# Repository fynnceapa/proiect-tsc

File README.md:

# OpenBook Project for Systems Testing
# Stan Andrei Razvan (Group 333CA)  

## Block Diagram

## Steps took
I followed the schematic and board layout provided by the teacher as closely as I could in Fusion 360.

The problems started when I began placing the components on the board. Most of the difficulties were related to identifying which discrete components to place and where, in order to make the routing process easier and more efficient.

I decided to route the board using two layers—top and bottom—and used vias where necessary. My lack of routing skills comes from the fact that i did not play around in Fusion that much...

## Core Components  

### 1. ESP32-C6 Microcontroller (Main Board)  
- **Processor:** 32-bit RISC-V @ 160MHz  
- **Wireless:** Wi-Fi 6 (802.11ax) + Bluetooth 5  
- **Memory:**  
  - 320KB RAM  
  - 512KB internal Flash (expandable via external NOR Flash)  
- **I/O:** 30+ GPIOs supporting SPI, I2C, UART, USB 2.0  

### 2. Peripheral Modules  

| Module          | Interface | Speed       | Key ESP32-C6 Pins       |  
|-----------------|-----------|-------------|-------------------------|  
| E-Paper Display | SPI       | 10-40 MHz   | `EPD_CS`, MOSI, SCK     |  
| BME688 Sensor   | I2C       | 400 kHz     | SCL, SDA                |  
| DS3231 RTC      | I2C       | 100 kHz     | SCL, SDA                |  
| NOR Flash       | SPI/QSPI  | 133 MHz     | `FLASH_CS`, MOSI, SCK   |  
| SD Card         | SPI       | 25 MHz      | `SS_SD`, MOSI, SCK      |  

## Module Specifications  

### A. E-Paper Display  
- **Type:** SPI-based (e.g., Waveshare)  
- **Key Pins:**  
  - `EPD_RST`: Hardware reset  
  - `EPD_DC`: Data/command control  
  - `EPD_BUSY`: Status monitoring  
- **Power:**  
  - 150mA (active refresh)  
  - 0mA (static display)  

### B. BME688 Environmental Sensor  
- **Metrics:** Temperature, humidity, pressure, VOC  
- **Accuracy:** ±0.5°C, ±3% RH  
- **Power:** 3.6mA (active), 2.1µA (sleep)  

### C. DS3231 Real-Time Clock  
- **Precision:** ±2ppm (±1min/year)  
- **Features:** Battery backup (`VBAT`), alarm interrupts (`INT_RTC`)  

### D. Storage Systems  
- **NOR Flash (W25Q512JVEIQ):**  
  - 64MB capacity  
  - QSPI @ 133MHz  
- **SD Card:**  
  - SPI interface @ 25MHz  

### E. Power Management  
- **Charger:** MCP73831 (Li-Po, 5V USB → 4.2V)  
- **LDO Regulator:** XC6220A331MR-G (3.3V logic)  
- **Battery Monitor:** MAX17048G+T10 (I2C)  

## Power Analysis  
| Mode             | Current Draw | Runtime* |  
|------------------|--------------|----------|  
| Active Operation | ~230mA       | ~4h      |  
| Deep Sleep       | ~6µA         | ~2 years |  

*With 1000mAh Li-Po battery  

## Low-Power Design Strategies  
- Deep-sleep mode with RTC wake-up  
- Selective peripheral power control  
- SPI/I2C bus deactivation when idle  

## Pinout Summary  

| Function            | Key Pins                 | Purpose                          |  
|---------------------|--------------------------|----------------------------------|  
| **E-Paper**         | `EPD_CS`, `EPD_DC`       | Display control                  |  
| **NOR Flash**       | `FLASH_CS`               | External memory access           |  
| **RTC**            | `INT_RTC`, `32KHZ`       | Timekeeping & alarms             |  
| **BME688**         | `SCL`, `SDA`             | Environmental sensing            |  
| **Power**          | `VBAT`, `3V3`            | Battery & regulated power        |

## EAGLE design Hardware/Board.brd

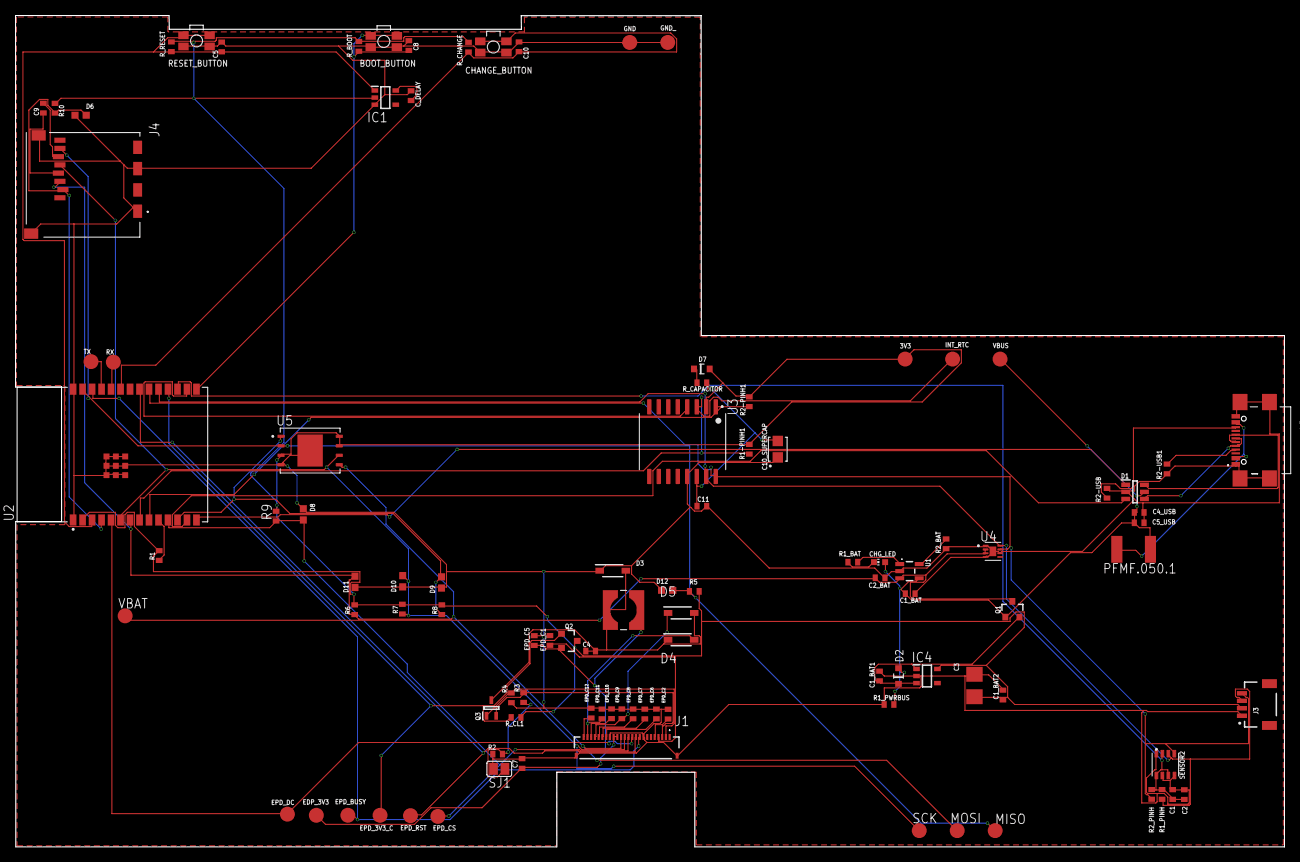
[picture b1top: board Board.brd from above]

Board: 2 copper layers, 169.8 x 111.2 mm, 103 parts (0 on the bottom side), 56 nets.

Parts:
3V3: TPTP20R; TP20R
BOOT_BUTTON: BUTTON_CUSYOMV1; MYBUTTON
C1, C2: 100nF; ESP32_WROVER_EAGLE-LTSPICE_C0402
C1_BAT, C1_BAT1, C1_BAT2, C2_BAT, C5_USB: 4.7uF; EAGLE-LTSPICE_C0402
C3: 100uF TANT; RCL_CT3528
C4: 4.7uF/25V; EAGLE-LTSPICE_C0402
C4_USB, C8, C10, C11: 100nF; EAGLE-LTSPICE_C0402
C5: 1uF; EAGLE-LTSPICE_C0402
C7: 10uF; EAGLE-LTSPICE_C0402
C9: EAGLE-LTSPICE_C0402
C10_SUPERCAP: CPH3225A; CAPCP3225X100N
CHANGE_BUTTON: BUTTON_CUSYOMV1; MYBUTTON
CHG_LED: ADAFRUIT_CHIP-LED0603
C_DELAY: 100nF; EAGLE-LTSPICE_C0402
D1: USBLC6-2SC6Y; SOT95P280X145-6N
D2, D7: ESP32_WROVER_AVX---SD0805S020S1R0_AVX_SD0805S020S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; ESP32_WROVER_AVX---SD0805S020S1R0_AVX_SD0805S020S1R0_0
D3, D4, D5: MBR0530; SOD3716X135N
D6, D8, D9, D10, D11, D12: PGB1010603MR; DIOC1608X36N
EDP_3V3: TPTP20R; TP20R
EPD_3V3_C: TPTP20R; TP20R
EPD_BUSY: TPTP20R; TP20R
EPD_C1, EPD_C2, EPD_C6, EPD_C7, EPD_C8, EPD_C9, EPD_C10, EPD_C11, EPD_C12: 1uF/50V; EAGLE-LTSPICE_C0402
EPD_C5: 0.1uF/50V; EAGLE-LTSPICE_C0402
EPD_CS: TPTP20R; TP20R
EPD_DC: TPTP20R; TP20R
EPD_RST: TPTP20R; TP20R
GND: TPTP20R; TP20R
GND_: TPTP20R; TP20R
IC1: BD5229G-TR; SOT95P280X125-5N
IC4: XC6220A331MR-G; SOT95P280X120-5N
INT_RTC: TPTP20R; TP20R
J1: FH34SRJ-24S-0.5SH_99_; FH34SRJ24S05SH99
J2: SAMACSYS_PARTS_USB4110-GF-A; SAMACSYS_PARTS_USB4110GFA
J3: QWIIC_RIGHT_ANGLE; JST04_1MM_RA
J4: 112A-TAAR-R03_ATTEND; 112ATAARR03ATTEND
L1: 68uH; IND_4828-WE-TPC_WRE
MISO: TPTP20R; TP20R
MOSI: TPTP20R; TP20R
PFMF.050.1: ESP32C6_VARISTORCN1812; ESP32C6_VARISTOR_CT/CN1812
Q1, Q2: 20V/4.2A/52mΩ/1.4W; ESP32_WROVER_SPARKFUN-DISCRETESEMI_SOT23-3
Q3: SI1308EDL-T1-GE3; SOT65P210X110-3N
R1, R4: 10K; ESP32_WROVER_EAGLE-LTSPICE_R0402
R1-PINH1, R2-PINH1, R5, R6, R7, R8, R9, R10: 10k; ESP32_WROVER_EAGLE-LTSPICE_R0402
R1_BAT: 200; ESP32_WROVER_EAGLE-LTSPICE_R0402
R1_PINH, R2_PINH: ESP32_WROVER_EAGLE-LTSPICE_R0402
R1_PWRBUS: 100k; ESP32_WROVER_EAGLE-LTSPICE_R0402
R2: 2.2; ESP32_WROVER_EAGLE-LTSPICE_R0402
R2-USB, R2-USB1: 5k1; ESP32_WROVER_EAGLE-LTSPICE_R0402
R2_BAT: 2k; ESP32_WROVER_EAGLE-LTSPICE_R0402
R3: 0.47; ESP32_WROVER_EAGLE-LTSPICE_R0402
RESET_BUTTON: BUTTON_CUSYOMV1; MYBUTTON
RX: TPTP20R; TP20R
R_BOOT: 10k; ESP32_WROVER_EAGLE-LTSPICE_R0402
R_CAPACITOR: 15; ESP32_WROVER_EAGLE-LTSPICE_R0402
R_CHANGE: 10k; ESP32_WROVER_EAGLE-LTSPICE_R0402
R_CL1: 10K; ESP32_WROVER_EAGLE-LTSPICE_R0402
R_RESET: 10k; ESP32_WROVER_EAGLE-LTSPICE_R0402
SCK: TPTP20R; TP20R
SENSOR2: BME688; ESP32_WROVER_BME680_PSON80P300X300X100-8N
SJ1: SJ
TX: TPTP20R; TP20R
U1: ESP32_WROVER_SPARKFUN-IC-POWER_MCP73831; ESP32_WROVER_SPARKFUN-IC-POWER_SOT23-5
U2: ESP32-C6-WROOM-1-N8; XCVR_ESP32-C6-WROOM-1-N8
U3: DS3231SN#; SOIC127P1032X265-16N
U4: MAX17048G+T10; SON50P200X200X80-9N
U5: W25Q512JVEIQ; SON127P600X800X80-9N
VBAT: TPTP20R; TP20R
VBUS: TPTP20R; TP20R

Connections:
3V3: 3V3.TP, C1_BAT2.1, C3.+, D7.2, IC1.2, IC4.5, J3.2, Q2.3, R1.2, R1-PINH1.2, R2-PINH1.2, R5.2, R6.2, R7.2, R8.2, R9.2, R10.2, R_BOOT.2, R_CHANGE.2, R_CL1.2, R_RESET.2, U2.2, U3.2, U5.3, U5.7, U5.8
32KHZ: R2-PINH1.1, U2.9, U3.1
DN: D1.4, J2.A7, J2.B7
DP: D1.6, J2.A6, J2.B6
EPD_3V3: C7.1, EDP_3V3.TP, EPD_C5.1, J1.15, J1.16, L1.2, Q2.2
EPD_3V3_C: EPD_3V3_C.TP, Q2.1, R_CL1.1, U2.18
EPD_BUSY: EPD_BUSY.TP, J1.9, U2.26
EPD_CS: D8.2, EPD_CS.TP, J1.12, R9.1, U2.11
EPD_DC: EPD_DC.TP, J1.11, U2.5
EPD_RST: EPD_RST.TP, J1.10, U2.21
FLASH_CS: D9.2, R8.1, U2.12, U5.1
GDR: J1.2, Q3.1, R4.2
GND: BOOT_BUTTON.1, BOOT_BUTTON.2, C1.2, C1_BAT.2, C1_BAT1.2, C1_BAT2.2, C2.2, C2_BAT.2, C3.-, C4_USB.2, C5.2, C5_USB.2, C7.2, C8.2, C10.2, C10_SUPERCAP.1, C11.2, CHANGE_BUTTON.1, CHANGE_BUTTON.2, C_DELAY.2, D1.2, D3.1, D6.1, D8.1, D9.1, D10.1, D11.1, D12.1, EPD_C1.2, EPD_C2.2, EPD_C5.2, EPD_C6.2, EPD_C7.2, EPD_C8.2, EPD_C9.2, EPD_C10.2, EPD_C11.2, EPD_C12.2, GND.TP, GND_.TP, IC1.3, IC4.2, J1.8, J1.17, J1.MP1, J1.MP2, J2.A1, J2.A12, J2.B1, J2.B12, J2.MP1, J2.MP2, J2.MP3, J2.MP4, J3.1, J4.G1, J4.G2, J4.G3, J4.G4, R1_PWRBUS.1, R2.1, R2-USB.2, R2-USB1.1, R2_BAT.1, R4.1, RESET_BUTTON.1, RESET_BUTTON.2, SENSOR2.1, SENSOR2.5, SENSOR2.7, SJ1.1, U1.2, U2.1, U2.28, U2.29_1, U2.29_2, U2.29_3, U2.29_4, U2.29_5, U2.29_6, U2.29_7, U2.29_8, U2.29_9, U3.13, U4.1, U4.4, U4.6, U4.9, U5.4, U5.9
GPIO8: R1.1, U2.10
I2C_PW: C1.1, C2.1, R1_PINH.2, R2_PINH.2, SENSOR2.2, SENSOR2.6, SENSOR2.8, U2.17
INT_RTC: INT_RTC.TP, R1-PINH1.1, U2.8, U3.3
IO/BOOT: BOOT_BUTTON.3, BOOT_BUTTON.4, C8.1, R_BOOT.1, U2.15
IO/CHANGE: C10.1, CHANGE_BUTTON.3, CHANGE_BUTTON.4, R_CHANGE.1, U2.23
MISO: D12.2, J4.P7, MISO.TP, R5.1, U2.27, U5.2
MOSI: D11.2, J1.14, J4.P3, MOSI.TP, R6.1, U2.7, U5.5
unnamed: C9.1, J4.P4
unnamed: J2.B5, R2-USB.1
unnamed: J2.A5, R2-USB1.2
unnamed: C1_BAT1.1, D2.1, IC4.1, IC4.3, Q1.2
unnamed: R1_BAT.2, U1.1
unnamed: CHG_LED.C, R1_BAT.1
unnamed: R2_BAT.2, U1.5
unnamed: EPD_C1.1, J1.4
unnamed: EPD_C2.1, J1.5
unnamed: EPD_C6.1, J1.18
unnamed: EPD_C7.1, J1.19
unnamed: EPD_C8.1, J1.20
unnamed: EPD_C10.1, J1.22
unnamed: EPD_C12.1, J1.24
unnamed: C_DELAY.1, IC1.5
unnamed: D7.1, R_CAPACITOR.1
unnamed: C9.2, J4.P6
PREVGH: D5.1, EPD_C9.1, J1.21
PREVGL: D4.2, EPD_C11.1, J1.23
RESE: J1.3, Q3.2, R3.2
RESE': R2.2, R3.1, SJ1.2
RESET: C5.1, IC1.1, RESET_BUTTON.3, RESET_BUTTON.4, R_RESET.1, U2.3
RTC_RST: U2.16, U3.4
RX: RX.TP, U2.24
SCK: D10.2, J1.13, J4.P5, R7.1, SCK.TP, U2.6, U5.6
SCL: J3.4, R2_PINH.1, SENSOR2.4, U2.20, U3.16, U4.7
SDA: J3.3, R1_PINH.1, SENSOR2.3, U2.19, U3.15, U4.8
SRC: C4.1, C4.2, D3.2, D4.1, D5.2, L1.1, Q3.3
SS_SD: D6.2, J4.P2, R10.1, U2.4
TX: TX.TP, U2.25
USB_D+: D1.1, U2.14
USB_D-: D1.3, U2.13
VBAT: C2_BAT.1, Q1.3, U1.3, U4.2, U4.3, VBAT.TP
VBUS: C1_BAT.1, C4_USB.1, C5_USB.1, CHG_LED.A, D1.5, D2.2, PFMF.050.1.2, Q1.1, R1_PWRBUS.2, U1.4, VBUS.TP
VRTC: C10_SUPERCAP.2, C11.1, R_CAPACITOR.2, U3.14
VUSB: J2.A4, J2.A9, J2.B4, J2.B9, PFMF.050.1.1

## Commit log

2025-04-04 init
2025-04-04 The structure
2025-04-04 files
2025-04-04 readme1
2025-04-04 readme2+schema
2025-04-04 removed gitignore from repo
2025-04-06 nope
2025-04-06 finished board
2025-04-06 readme
2025-04-06 final changes on board
2025-04-06 Manufacturing
2025-04-06 images and 3d file
2025-04-10 modified schematic (added names of the components)
2025-04-10 fixed names on board so its readable
2025-04-11 Create image folder
2025-04-11 images
2025-04-11 Create mechanical
2025-04-11 3d board

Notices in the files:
parts and their libraries:
COPYRIGHT: Copyright (C) 2024 Ultra Librarian. All rights reserved.
